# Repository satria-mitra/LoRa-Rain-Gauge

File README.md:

# <div style="text-align: center;" markdown="1">LoRa Rain Gauge</div>

This repository contains an Arduino sketch for a rain gauge system that utilizes LoRa communication, RTC for timestamping, and an SD card for data logging.

*CASA0016:MDB*\
Satria Mitra Utama

# Dependancies
## Hardware Requirements
1. Arduino MKR board with LoRa connectivity
2. DS3231 RTC module
3. SD card module
4. Reed switch for rainfall measurement
5. 5mm Neodymum magnet
6. Printed Rain Gauge
7. 25mm screw with diameter 2mm
7. Lot of wires

### Optional Hardwares
1. Lipo Battery
2. Solar Panel
3. Adafruit Solar Charger

## Software
### Arduino Libraries
1. [RTCLib](https://www.arduino.cc/reference/en/libraries/rtclib/)
2. [MKRWAN](https://www.arduino.cc/reference/en/libraries/mkrwan/)
3. Wire
4. SD
5. SPI

### Node Red
1. [Node-Red Dashboard lib](https://flows.nodered.org/node/node-red-dashboard)

# Getting Started
1. **Connections**: Wire up the components according to the provided pin configurations. 

| No | Hardware | Hardware Pin | Arduino MKR Pin |
|----|----------|--------------|-------------|
|1   | RTC      |    VCC       |VCC          |
|    |          | GND          | GND         |
|    |          | SCL          | SCL/12      |
|    |          | SDA          | SDA/11 |
|2   | Sd card  |    VCC       |VCC          |
|    |          | GND          | GND         |
|    |          | MOSI         | 8/MOSI      |
|    |          | MISO         | 10/MISO     |
|    |          | SCK          | 7           |
|3   | Reed switch| SW1        | 6           |
|    |       | VCC          | VCC         |
|    |          | GND          | GND         |
|4   | Charger | JST +        | JST +        |
|    |          | JST-         | JST -       |

2. **Rain Gauge**:
   - Print these files using PLA (not waterproof) or PETG(waterproof) filament 
     - rain_gauge-can.stl
     - rain_gauge-bucket.stl
     - rain_gauge-base.stl
   - Insert your 5mm neodymum magnet into the side hole of bucket
   - Use long shaft/screw to insert the bucket into the base
   - Plug the reed switch module into base. Final piece of Rain Gauge should looks like this

2. **Libraries**: Install the necessary libraries (Wire, RTClib, MKRWAN, SPI, SD) in the Arduino IDE.
3. **TTN Application**:
   - Sign up for The Things Network
   - Select your region and [create your application on TTN console](https://www.thethingsindustries.com/docs/integrations/adding-applications/)
   - Plug your Arduino MKRWAN and run a script from Arduino IDE>Examples>MKRWAN>First Configuration, take a note on your DevUI
   - [Register your End Device on TTN Console ](https://workshops.cetools.org/codelabs/CASA0016-Workshop-4/index.html?index=..%2F..casa0016#6)
   - Create a file named __arduino_secrets.h__ on the same folder of Arduino LoRa Transmitter scripts and copy paste your appEui and appKey from TTN Console

     ```
     const char *appEui = "0000000000000000";
     const char *appKey = "<APP_KEY>";
     ``` 
4. Upload the scripts of Transmitter and see live data on TTN Console
5. If you can see your data, congratulations, if not please do see Troubleshooting sections
6. [Install Node-Red](https://nodered.org/docs/getting-started/) on your Raspberry PI or on your PC
7. [Install Node-Red Dashboard library](https://flows.nodered.org/node/node-red-dashboard)
8. Import Node-Red json files configuration from Scripts>Node-Red
9. See the payload on the debug message on Node-red. You can modify or create your own dashboard. Done

# Functionality
### RTC Setup
- Sets up and initializes the DS3231 RTC module for accurate timekeeping.
- Handles RTC power loss scenarios by setting the time using the sketch compilation time if power is lost.

### Rain Measurement
- Monitors rainfall using a reed switch and software debouncing to count pulses accurately.
- Resets accumulated rainfall at midnight to start afresh.

### LoRa Communication and Data Logging
- Sends rain gauge data via LoRaWAN to TTN at regular intervals.
- Logs data (date, time, accumulated rainfall) onto an SD card in a CSV format for local storage.

### Usage
- Monitor the Serial Monitor to observe real-time data and system status.
- Access the `rain.txt` file on the SD card for detailed logged rain gauge data.

## Troubleshooting
- If encountering issues during LoRa connection, ensure proper positioning for signal reception.
- Check your appKey and appEui on TTN Console and your aduino_secrets.h
- Verify wiring connections and component compatibility.
- Dont forget to attach your antenna

## Future Work
- Use low power library
- Design a watertight enclosure

## Reflective learning
- Prototype and iterate to make it better
- Outdoor device needs a waterproof and watertight material

## License
This project is licensed under the MIT License.

## Credits
- Dusan DJ for his awesome tipping buckets

## Acknowledgements
- Arduino community
- Libraries used: RTClib, MKRWAN, SD
- Node Red

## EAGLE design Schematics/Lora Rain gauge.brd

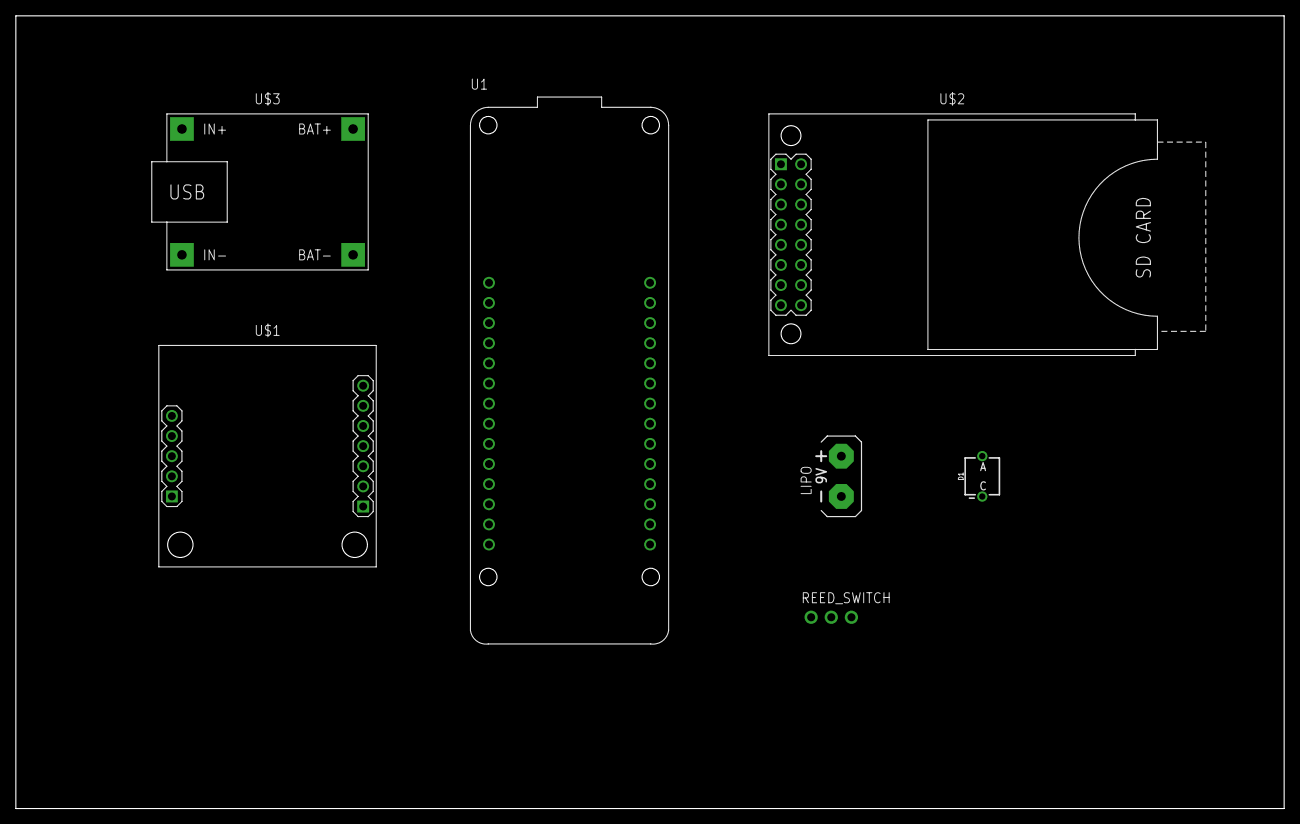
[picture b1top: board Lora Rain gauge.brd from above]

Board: 2 copper layers, 160.0 x 100.0 mm, 7 parts (0 on the bottom side), 12 nets, no tracks yet.

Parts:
D1: BPW34
LIPO: AB9V
REED_SWITCH: 1X03-CLEANBIG
U1: ARDUINO_MKR_WAN_1310; BOARD_ARDUINO_MKR_WAN_1310
U$1: RTC-EEPROM-BATTERY; RTC_EEPROM_BATTERY
U$2: CARD-SD-ADAPTER
U$3: BATTERY-CHARGER-LI-5V

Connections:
BAT+: LIPO.+, U$3.BAT+
BAT-: LIPO.-, U$3.BAT-
CS: U1.J5_2, U$2.7
GND: REED_SWITCH.2, U1.J5_11, U$1.J1.1, U$2.1
GND.2: U$1.J2.2, U$2.15
MISO: U1.J5_5, U$2.13
MOSI: U1.J5_3, U$2.9
SCK: U1.J5_4, U$2.11
SCL: U1.J5_7, U$1.J1.4
SDA: U1.J5_6, U$1.J1.3
SW1: REED_SWITCH.3, U1.J3_13
VCC: REED_SWITCH.1, U1.J5_12, U$1.J1.2, U$2.5

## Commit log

2023-12-10 Upload 3d models of rain bucket
2023-12-10 Initial commit of transmitter scripts
2023-12-10 Add arduino secret for TTN App
2023-12-12 upload 3d file
2023-12-13 Create LICENSE
2024-01-10 update github
2024-01-10 [ImgBot] Optimize images
    *Total -- 1,157.80kb -> 1,006.51kb (13.07%)
    /Assets/Pictures/design concept.png -- 121.10kb -> 82.81kb (31.62%)
    /Assets/Pictures/Schematics.png -- 33.70kb -> 25.96kb (22.95%)
    /Assets/Pictures/Enclosure.png -- 23.55kb -> 18.55kb (21.25%)
    /Assets/Pictures/Node-red.png -- 11.07kb -> 8.78kb (20.69%)
    /Assets/Pictures/Tipping_bucket.png -- 188.55kb -> 153.94kb (18.35%)
2024-01-11 upload the code and pictures
2024-01-11 remove duplicate files
2024-01-11 upload schematics
2024-01-11 Update readme file
2024-01-11 upload license
2024-01-11 update readme files
2024-01-13 upload gitignore
2024-01-13 gitignore

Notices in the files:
parts and their libraries:
SparkFun-Sensors: Licensing: Creative Commons ShareAlike 4.0 International - https://creativecommons.org/licenses/by-sa/4.0
diy-modules: Released under the Creative Commons Attribution 4.0 International License: http://creativecommons.org/licenses/by/4.0
